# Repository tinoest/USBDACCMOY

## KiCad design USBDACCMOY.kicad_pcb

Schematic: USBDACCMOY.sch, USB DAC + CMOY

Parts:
SYM1: SYM_ESD_Small; ESD-Logo_6.6x6mm_SilkScreen

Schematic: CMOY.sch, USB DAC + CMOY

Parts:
C1, C6: 0.1uF; CAPACITOR-WIMA_C5B5
C2, C4: 220uF; CP_Elec_6.3x5.3
C3, C5: 0.068uF; CAPACITOR-WIMA_C2.5-2
C19: C; C_0805_HandSoldering
IC1: OPA2134P; SOIC-8-N
JACK-OUT1: STEREOJACK; STX3100
L2: L; C_0805_HandSoldering
M1: AUDIO-POTS_ALPS_RK0971221Z05; AUDIO-POTS_ALPS_RK0971221Z0X
R1, R5: 47R; R_0805
R2, R6: 100k; R_0805
R3, R7: 10k; R_0805
R4, R8: 2k; R_0805
U1: NMA0512SC; DCDC-Conv_muRata_NMAxxxxSC

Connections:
/CMOY/L+: C1.1, IC1.5 (+IN), R2.2
/CMOY/L-: IC1.6 (-IN), R3.2, R4.2
/CMOY/OP-L: IC1.7 (OUT), R1.2
/CMOY/OP-R: IC1.1 (OUT), R5.2
/CMOY/R+: C6.1, IC1.3 (+IN), R6.2
/CMOY/R-: IC1.2 (-IN), R7.2, R8.2
/CMOY/VOLUME-OUT-L: C1.2, M1.O1 (2)
/CMOY/VOLUME-OUT-R: C6.2, M1.O2 (2)
GND: C19.2, U1.2 (VIN-); also elsewhere on the board
INPUT_L: M1.I1 (3); also elsewhere on the board
INPUT_R: M1.I2 (3); also elsewhere on the board
unnamed: C19.1, L2.2, U1.1 (VIN+)
unnamed: L2.1, M1.S2
OUTPUT_L: JACK-OUT1.2, R1.1, R3.1
OUTPUT_R: JACK-OUT1.5, R5.1, R7.1
V+: C2.1 (+), C3.2, IC1.8 (V+), U1.6 (VOUT+)
V-: C4.2 (-), C5.1, IC1.4 (V-), U1.4 (VOUT-)
VBUS: M1.S1; also elsewhere on the board

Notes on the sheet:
Gain = R5/R4 + 1
Gain = 6

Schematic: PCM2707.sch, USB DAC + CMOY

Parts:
C7, C8: 100uF; CP_Elec_6.3x5.3
C9, C10: 22nF; C_0805
C11, C12, C14, C15, C16: 1uF; C_0805
C13: 10uF; CP_Elec_5x5.3
C17, C18: 22pF; C_0805
CON1: GND_CONNECTORSMD; GND_CONNECTOR
DOUT1: 87758-0216; CON-MOLEX_87758-0216
J1: USB; MOLEX-47346-0001_MOLEX_47346-0001
JP1: CONNECTORS_1X05_LOCK
L1: 1A FB; PASSIVES_0805
LED1, LED2: Blue; LED_LED-0603
OUTPUT1: AUDIO; CON-LSTB_MA03-1
Q1: 12MHz; CRYSTAL_HC49U-V
R9, R10, R11, R12: 3.3kOhm; R_0805
R13, R14: 16Ohm; R_0805
R15: 560Ohm; R_0805
R16: 330Ohm; R_0805
R17, R21: 1.5kOhm; R_0805
R18, R19: 22Ohm; R_0805
R20: 1MOhm; R_0805
SV1: USB-WIRE; CON-LSTB_MA04-1
U2: PCM2707C

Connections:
/PCM2707//SSPND: LED2.1, U2.11 (SSPND)
/PCM2707/D+: J1.3, R17.1, R18.2, SV1.3
/PCM2707/D-: J1.2, R19.2, SV1.2
/PCM2707/N$1: JP1.5, U2.6 (HID0)
/PCM2707/N$2: C14.2, U2.2 (VCCP)
/PCM2707/N$3: JP1.4, U2.7 (HID1)
/PCM2707/N$4: C13.1 (+), U2.32 (VCOM)
/PCM2707/N$5: JP1.3, U2.8 (HID2)
/PCM2707/N$6: DOUT1.1, U2.17 (DOUT)
/PCM2707/N$7: C17.1, Q1.1, R20.1, U2.12 (XTI)
/PCM2707/N$8: C18.1, Q1.2, R20.2, U2.13 (XTO)
/PCM2707/N$9: R18.1, U2.23 (D+)
/PCM2707/N$10: R19.1, U2.22 (D-)
/PCM2707/N$13: C11.2, U2.30 (VCCR)
/PCM2707/N$14: LED1.2, R15.2
/PCM2707/N$15: R21.2, U2.15 (DT)
/PCM2707/N$16: C12.1, U2.27 (VCCL)
/PCM2707/N$17: C10.2, R14.2
/PCM2707/N$18: C9.2, R13.2
/PCM2707/N$21: C8.1 (+), C10.1, R10.2, U2.29 (VOUTR)
/PCM2707/N$22: LED2.2, R16.2
/PCM2707/N$23: C7.1 (+), C9.1, R9.2, U2.28 (VOUTL)
GND: C13.2 (-), C14.1, C15.2, C16.2, C17.2, C18.2, CON1.2 (DGND), DOUT1.2, J1.5, JP1.1, R15.1, R16.1, SV1.4, U2.1 (PGND), U2.3 (HOST), U2.20 (DGND); also elsewhere on the board
INPUT_L: C7.2 (-), OUTPUT1.3, R11.2; also elsewhere on the board
INPUT_R: C8.2 (-), OUTPUT1.2, R12.2; also elsewhere on the board
unnamed: C15.1, L1.1, U2.24 (VBUS)
VBUS: J1.1, JP1.2, L1.2, LED1.1, SV1.1; also elsewhere on the board
VDD: C16.1, R17.2, R21.1, U2.9 (FSEL), U2.10 (TEST), U2.16 (PSEL), U2.21 (VDD)

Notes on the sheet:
VDD
/SSPND
VBUS
GND

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
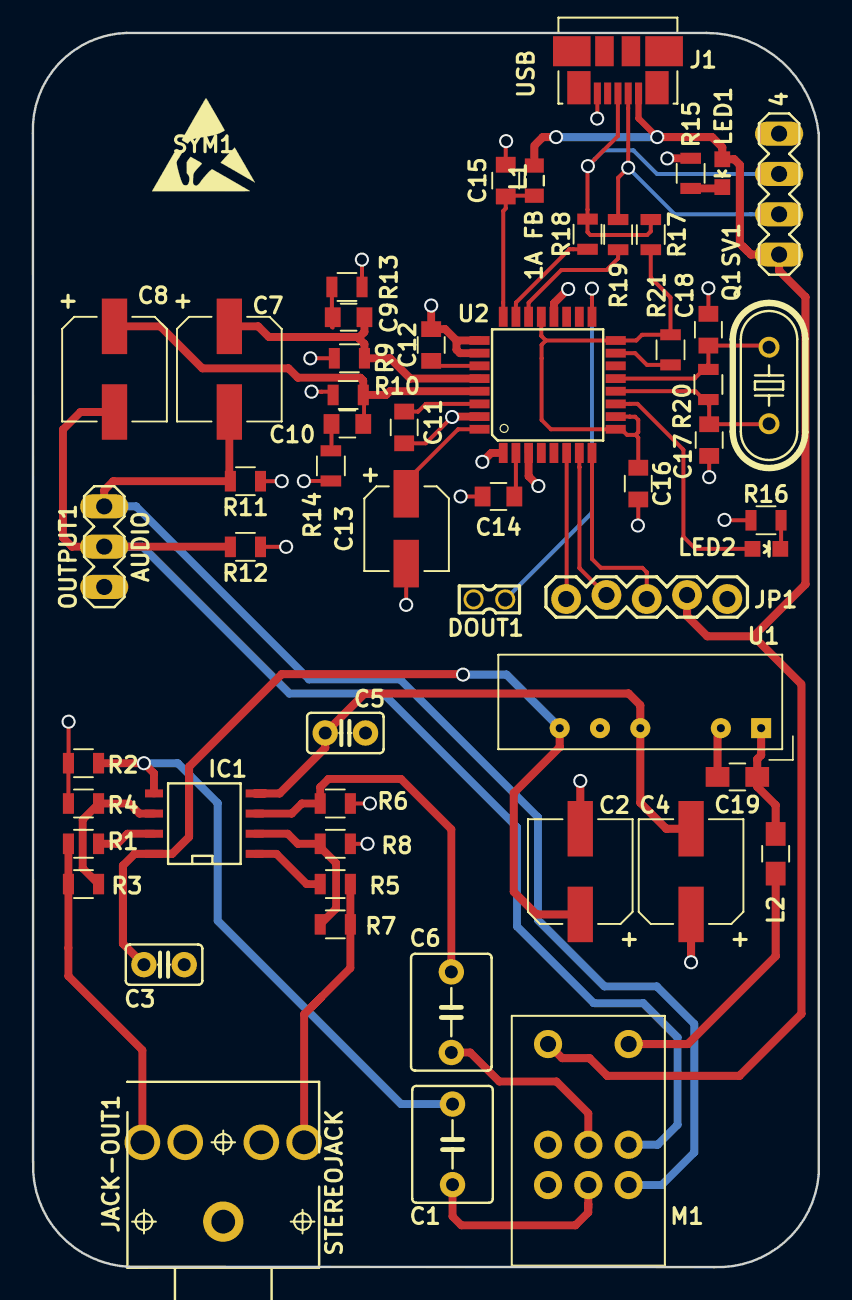
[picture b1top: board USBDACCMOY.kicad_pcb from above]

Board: 2 copper layers, 49.5 x 77.8 mm, 57 parts (0 on the bottom side), 43 nets.

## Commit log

2017-11-08 Adding USB PCM2707 + CMOY Schematic
    Added combination of PCM2707 and CMOY Schematics with DC/DC Converter,
    PCB not routed, schematic connections unchecked.
2017-11-09 Removed incorrectly named files
2017-11-09 Removed -bak file
2017-11-09 Added -bak to .gitignore
2017-11-09 Ignore .bak, .bck, -bak
    Oh for consistency…
2018-10-28 Updated to kicad 5.0 and started routing.
2020-06-27 Updated Design Files
2020-06-27 Removed old files
2020-07-04 Adding BOM
2020-07-05 Updated BOM, removed old one
2020-07-05 Removed lockfiles updated with costing
